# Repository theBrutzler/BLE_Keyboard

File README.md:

# BLE_Keyboard
I replaced my broken board of the schwaiger keyboard with an esp32 pico board

the inside close up

the complete inside incl. the bartery

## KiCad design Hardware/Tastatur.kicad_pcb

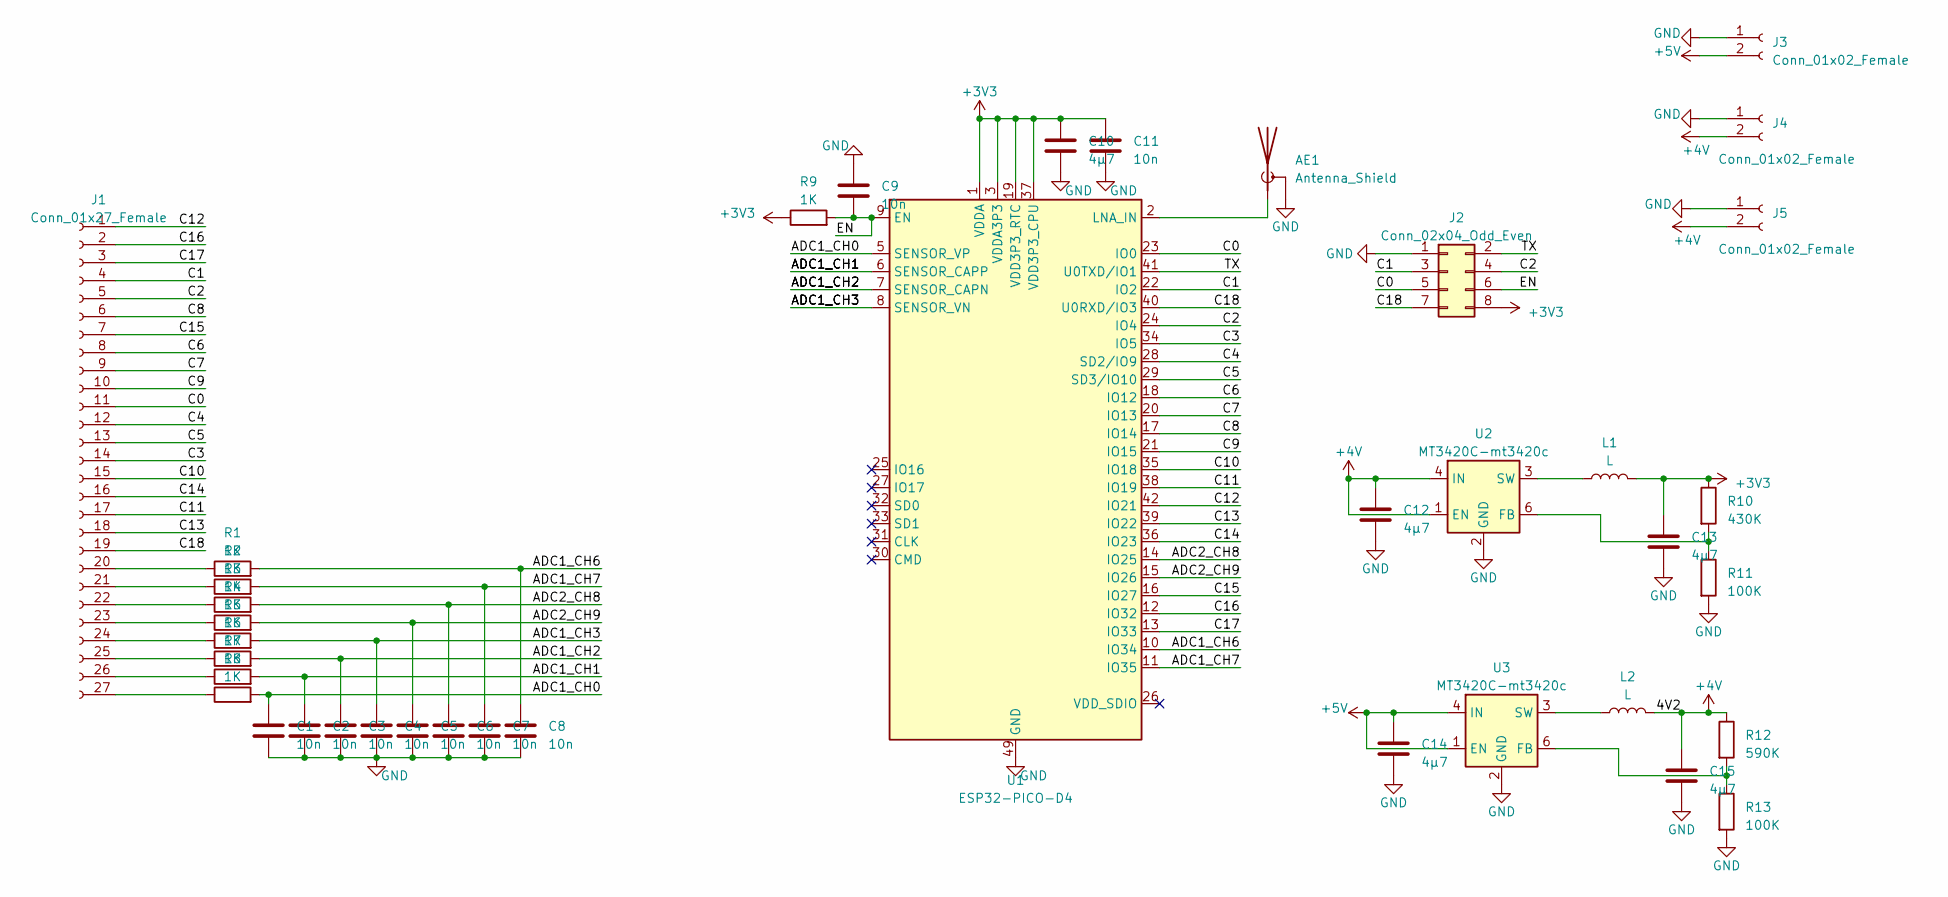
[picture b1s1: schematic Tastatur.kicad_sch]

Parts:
AE1: Antenna_Shield; Texas_SWRA117D_2.4GHz_Left
C1, C2, C3, C4, C5, C6, C7, C8, C9, C11: 10n; C_0402_1005Metric
C10, C12, C13, C14, C15: 4µ7; C_0805_2012Metric
J1: Conn_01x27_Female; SCHWAIGER_ESP_Connector
J2: Conn_02x04_Odd_Even; PinHeader_2x04_P2.54mm_Vertical
J3, J4, J5: Conn_01x02_Female; PinHeader_1x02_P1.27mm_Vertical
L1, L2: L; L_1008_2520Metric_Pad1.43x2.20mm_HandSolder
R1, R2, R3, R4, R5, R6, R7, R8, R9: 1K; L_0402_1005Metric
R10: 430K; L_0402_1005Metric
R11, R13: 100K; L_0402_1005Metric
R12: 590K; L_0402_1005Metric
U1: ESP32-PICO-D4; QFN-48-1EP_7x7mm_P0.5mm_EP5.3x5.3mm
U2, U3: MT3420C-mt3420c; SOT-23-6

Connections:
+3V3: C10.1, C11.1, C13.1, J2.8, L1.2, R9.1, R10.1, U1.1 (VDDA), U1.3 (VDDA3P3), U1.4 (VDDA3P3), U1.19 (VDD3P3_RTC), U1.37 (VDD3P3_CPU), U1.43 (VDDA), U1.46 (VDDA)
+4V: C12.1, C15.1, J4.2, J5.2, L2.2, R12.1, U2.1 (EN), U2.4 (IN)
+5V: C14.1, J3.2, U3.1 (EN), U3.4 (IN)
/ADC1_CH0: C1.1, R8.2, U1.5 (SENSOR_VP)
/ADC1_CH1: C2.1, R7.2, U1.6 (SENSOR_CAPP)
/ADC1_CH2: C3.1, R6.2, U1.7 (SENSOR_CAPN)
/ADC1_CH3: C4.1, R5.2, U1.8 (SENSOR_VN)
/ADC1_CH6: C8.1, R1.2, U1.10 (IO34)
/ADC1_CH7: C7.1, R2.2, U1.11 (IO35)
/ADC2_CH8: C6.1, R3.2, U1.14 (IO25)
/ADC2_CH9: C5.1, R4.2, U1.15 (IO26)
/C0: J1.11, J2.5, U1.23 (IO0)
/C1: J1.4, J2.3, U1.22 (IO2)
/C2: J1.5, J2.4, U1.24 (IO4)
/C3: J1.14, U1.34 (IO5)
/C4: J1.12, U1.28 (SD2/IO9)
/C5: J1.13, U1.29 (SD3/IO10)
/C6: J1.8, U1.18 (IO12)
/C7: J1.9, U1.20 (IO13)
/C8: J1.6, U1.17 (IO14)
/C9: J1.10, U1.21 (IO15)
/C10: J1.15, U1.35 (IO18)
/C11: J1.17, U1.38 (IO19)
/C12: J1.1, U1.42 (IO21)
/C13: J1.18, U1.39 (IO22)
/C14: J1.16, U1.36 (IO23)
/C15: J1.7, U1.16 (IO27)
/C16: J1.2, U1.12 (IO32)
/C17: J1.3, U1.13 (IO33)
/C18: J1.19, J2.7, U1.40 (U0RXD/IO3)
/EN: C9.2, J2.6, R9.2, U1.9 (EN)
/TX: J2.2, U1.41 (U0TXD/IO1)
GND: AE1.2 (Shield), C1.2, C2.2, C3.2, C4.2, C5.2, C6.2, C7.2, C8.2, C9.1, C10.2, C11.2, C12.2, C13.2, C14.2, C15.2, J2.1, J3.1, J4.1, J5.1, R11.2, R13.2, U1.49 (GND), U2.2 (GND), U3.2 (GND)
unnamed: AE1.1 (A), U1.2 (LNA_IN)
unnamed: J1.20, R1.1
unnamed: J1.21, R2.1
unnamed: J1.22, R3.1
unnamed: J1.23, R4.1
unnamed: J1.24, R5.1
unnamed: J1.25, R6.1
unnamed: J1.26, R7.1
unnamed: J1.27, R8.1
unnamed: L1.1, U2.3 (SW)
unnamed: L2.1, U3.3 (SW)
unnamed: R10.2, R11.1, U2.6 (FB)
unnamed: R12.2, R13.1, U3.6 (FB)

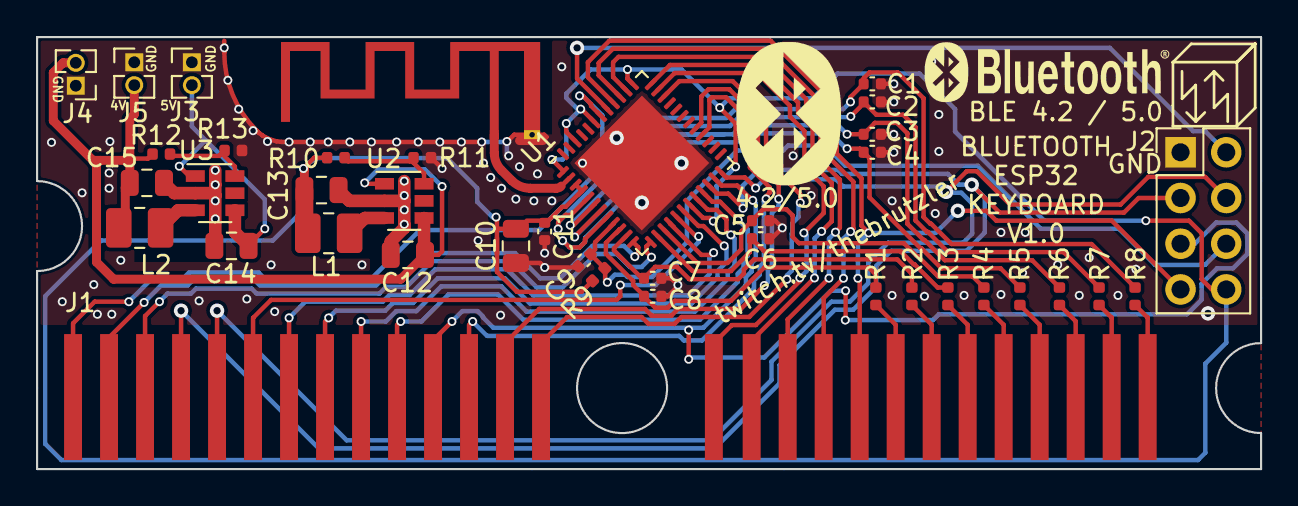
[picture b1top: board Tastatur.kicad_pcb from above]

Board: 2 copper layers, 68.0 x 24.0 mm, 40 parts (0 on the bottom side), 46 nets.

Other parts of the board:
SM3: SYM_Arrow45_Tiny; Symbol_kurzschlussblog

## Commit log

2021-10-04 Inital commit
2021-10-04 Upload pictures
2021-10-05 Solved #1
    #1 is now fixed for german keyboard
